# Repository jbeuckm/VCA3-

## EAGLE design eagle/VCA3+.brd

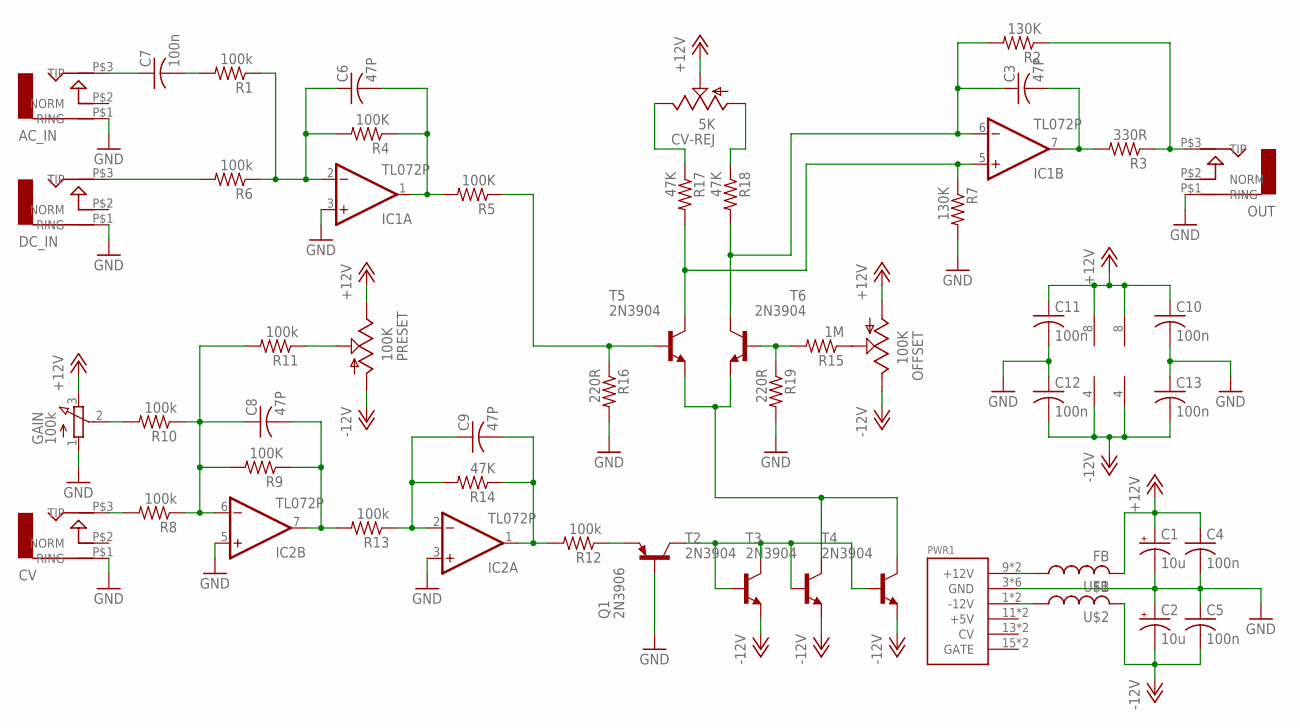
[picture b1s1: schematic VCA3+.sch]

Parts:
AC_IN: AUDIO-JACK; ERTHENVAR-JACK-90DEG
C1, C2: 10u; B45181A
C3, C6, C8, C9: 47P; C050-024X044
C4, C5, C7, C10, C11, C12, C13: 100n; C050-024X044
CV: AUDIO-JACK; ERTHENVAR-JACK-90DEG
CV-REJ: 5K; B64Y
DC_IN: AUDIO-JACK; ERTHENVAR-JACK-90DEG
GAIN: 100k; 3RP/1610N
IC1, IC2: TL072P; DIL08
OFFSET: 100K; B64Y
OUT: AUDIO-JACK; ERTHENVAR-JACK-90DEG
PRESET: 100K; B64Y
PWR1: POWER; POWER_16
Q1: 2N3906; TO92
R1, R6, R8, R10, R11, R12, R13: 100k; 0207/10
R2, R7: 130K; 0207/10
R3: 330R; 0207/10
R4, R5, R9: 100K; 0207/10
R14, R17, R18: 47K; 0207/10
R15: 1M; 0207/10
R16, R19: 220R; 0207/10
T2, T3, T4, T5, T6: 2N3904; TO92
U$1, U$2: FB

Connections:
+12V: C1.+, C4.1, C10.1, C11.1, CV-REJ.S, GAIN.3 (E), IC1.8 (V+), IC2.8 (V+), OFFSET.A, PRESET.E, U$1.P$2 (2)
-12V: C2.-, C5.2, C12.2, C13.2, IC1.4 (V-), IC2.4 (V-), OFFSET.E, PRESET.A, T2.3 (E), T3.3 (E), T4.3 (E), U$2.P$2 (2)
GND: AC_IN.P$1 (RING), C1.-, C2.+, C4.2, C5.1, C10.2, C11.2, C12.1, C13.1, CV.P$1 (RING), DC_IN.P$1 (RING), GAIN.1 (A), IC1.3 (+IN), IC2.3 (+IN), IC2.5 (+IN), OUT.P$1 (RING), PWR1.3 (GND), PWR1.4 (GND), PWR1.5 (GND), PWR1.6 (GND), PWR1.7 (GND), PWR1.8 (GND), Q1.2 (B), R7.2, R16.2, R19.2
unnamed: PWR1.9 (+12V), PWR1.10 (+12V), U$1.P$1 (1)
unnamed: PWR1.1 (-12V), PWR1.2 (-12V), U$2.P$1 (1)
unnamed: AC_IN.P$3 (TIP), C7.1
unnamed: C7.2, R1.2
unnamed: C3.2, IC1.7 (OUT), R3.2
unnamed: OUT.P$3 (TIP), R2.1, R3.1
unnamed: C6.1, IC1.2 (-IN), R1.1, R4.2, R6.1
unnamed: C6.2, IC1.1 (OUT), R4.1, R5.2
unnamed: IC1.5 (+IN), R7.1, R17.2, T5.1 (C)
unnamed: CV.P$3 (TIP), R8.2
unnamed: C8.1, IC2.6 (-IN), R8.1, R9.2, R10.1, R11.2
unnamed: GAIN.2 (S), R10.2
unnamed: PRESET.S, R11.1
unnamed: DC_IN.P$3 (TIP), R6.2
unnamed: C8.2, IC2.7 (OUT), R9.1, R13.2
unnamed: Q1.3 (E), R12.1
unnamed: C9.1, IC2.2 (-IN), R13.1, R14.2
unnamed: C9.2, IC2.1 (OUT), R12.2, R14.1
unnamed: Q1.1 (C), T2.1 (C), T2.2 (B), T3.2 (B), T4.2 (B)
unnamed: T3.1 (C), T4.1 (C), T5.3 (E), T6.3 (E)
unnamed: OFFSET.S, R15.1
unnamed: R5.1, R16.1, T5.2 (B)
unnamed: R15.2, R19.1, T6.2 (B)
unnamed: C3.1, IC1.6 (-IN), R2.2, R18.2, T6.1 (C)
unnamed: CV-REJ.E, R17.1
unnamed: CV-REJ.A, R18.1

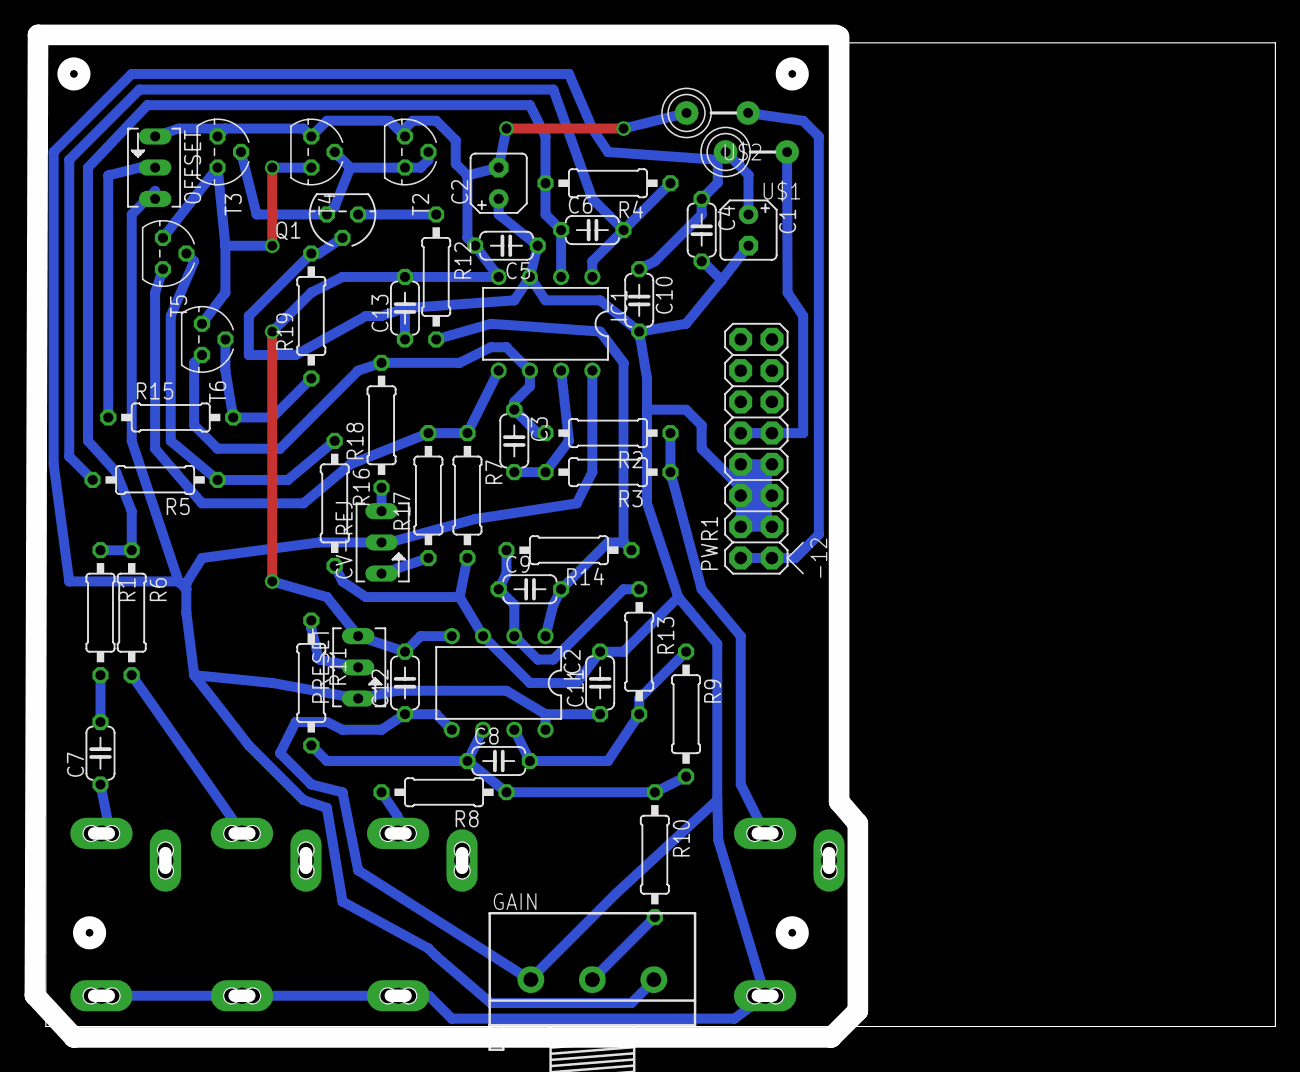
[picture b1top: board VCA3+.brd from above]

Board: 2 copper layers, 100.1 x 81.5 mm, 51 parts (0 on the bottom side), 29 nets.

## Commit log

2016-01-02 schematic
2016-01-02 layout begins
2016-01-03 schemo fix
2016-01-06 close to layout
2016-01-07 nearly routed
2016-01-08 routed
2016-01-08 cutout
2016-01-14 tweaked
2016-01-14 gcode
